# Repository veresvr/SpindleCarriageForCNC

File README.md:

# Spindle Carriage For CNC
:100: Project is done!

Milling carriage for my [laser CNC](https://github.com/veresvr/LaserCNCMachine)
All drawings available here [Drawings](https://github.com/veresvr/SpindleCarriageForCNC/tree/main/Drawings/AllDrawings.pdf)

##### Rendering
</img>
##### Assembly structure
 </img>

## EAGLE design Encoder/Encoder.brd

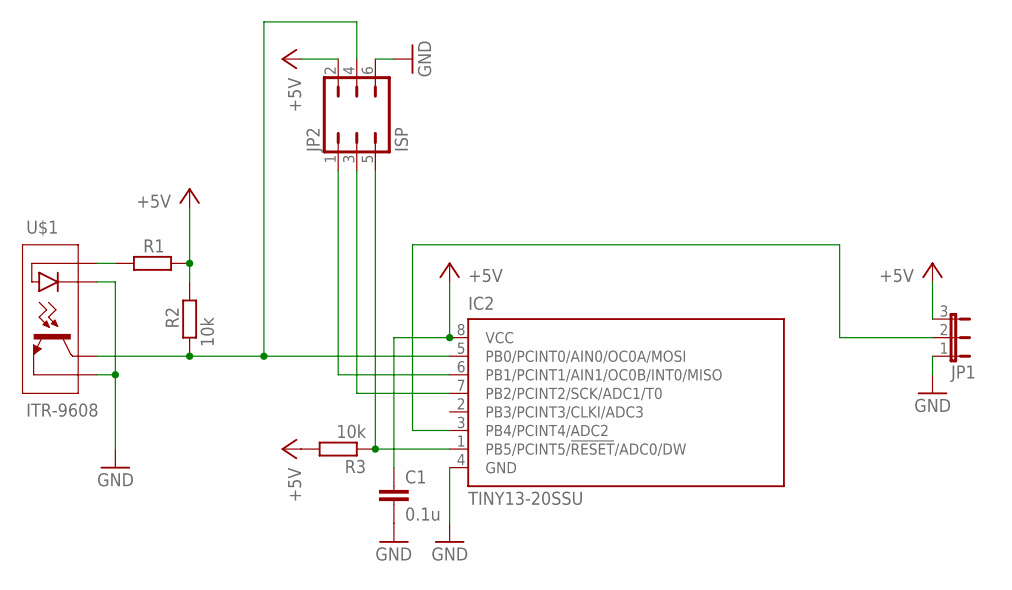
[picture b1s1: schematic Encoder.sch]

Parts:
C1: 0.1u; C0805
IC2: TINY13-20SSU; 8S1
JP1: JP2E; JP2
JP2: ISP; JP3Q
R1: R-EU_M0805; M0805
R2, R3: 10k; M0805
U$1: ITR-9608; ITR-9608-FOOTPRINT

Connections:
!RES: IC2.1 (PB5/PCINT5/!RESET!/ADC0/DW), JP2.5, R3.1
+5V: C1.1, IC2.8 (VCC), JP1.3, JP2.2, R1.2, R2.2, R3.2
DATA-IN: IC2.5 (PB0/PCINT0/AIN0/OC0A/MOSI), JP2.4, R2.1, U$1.C
DATA-OUT: IC2.3 (PB4/PCINT4/ADC2), JP1.2
GND: C1.2, IC2.4 (GND), JP1.1, JP2.6, U$1.E, U$1.K
unnamed: IC2.6 (PB1/PCINT1/AIN1/OC0B/INT0/MISO), JP2.1
unnamed: R1.1, U$1.A
unnamed: IC2.7 (PB2/PCINT2/SCK/ADC1/T0), JP2.3

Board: 2 copper layers, 8 parts (2 on the bottom side), 8 nets, no tracks yet.

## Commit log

2020-12-20 Some little bugs fixed
2021-01-02 Update files to SW2020. Some composition changes. Added more fasteners
2021-01-03 Some little composition changes.
2021-01-03 Simple motor encoder
2021-01-03 Change position of end sensors
2021-01-03 Decrease width of the CarriageBase
2021-01-03 Update CarriageBase
2021-01-05 Replace some screws
2021-01-05 Change geometry a little bit & add new screws
2021-01-07 Added ventilation holes to carriage. Updated encoder
2021-01-07 A little geometric changes
2021-01-08 Changed geometry for possibility using some drills.
2021-01-08 Hide threaded rod in carriage Z for decrease height
2021-01-10 Was decreased width in VerticalPlate
2021-01-10 A little changes in carriage cower
2021-01-16 Almost done the end sensors assembly
2021-01-17 End sensors assembly done. Added some little changes to VerticalPlate
2021-01-20 Changed lead screw length. Added some wires
2021-01-22 A little changes with cables and encoder
2021-01-30 Added mount to encoder
2021-01-31 Added motor & encoder wires
2021-02-10 Update motor mount
2021-02-22 Updated mates
2021-05-12 Updated the readme file
2021-05-21 Updated some parts. Added a drawing for sensor mount
2021-06-05 Updated parts
2021-06-09 Added drawings, updated material properties and tolerances in the parts. Added BOM
2021-06-12 Updated properties in the parts and the assemblies, updated the BOM. Added internet links to some positions in the BOM
2021-06-13 Added cable to the stepper, updated end sensor wire
2021-06-23 Added a scheme and a pcb for encoder
2021-06-27 Added a pcb for encoder: made scheme, library and prearranged components on the board
2021-06-27 Updated the assembly in case of encoder: added a pcb and updated the cover
2021-06-30 Added connector for programmer. Increased the place for the encoder.
2021-08-06 Added more powerful stepper motor
2021-08-07 Updated mount holes for the new stepper motor. Added cable for the stepper. Updated cable tie
2021-08-11 Tried making a new simplest tensioner
2021-08-20 Updated the tensioner and its mount.
2021-08-21 Updated the tensioner. Made TensionerBasePlate as a real part, updated properties, made drawing
2021-08-27 Updated the dimensions and tolerances in the tensioner plate. Updated some parameters in the parts.
2021-08-28 Updated properties for some parts. Updated tolerances. Added drawing numbers. Added some drawings
2021-08-29 Updated mount in motor holder
2021-09-13 Updated the drawing
2021-11-07 Added drawing for the tensioner and made it non virtual
2021-11-07 Added drawing for Carriage
2021-11-10 Updated the plastic mount brackets in the carriage
2021-11-11 Updated spacers and another part of the carriage
2021-11-20 Updated material in plastic parts.
2021-12-17 Packed all files into a single directory.
2021-12-18 Updated preview. Removed unnecessary stepper motor.
2022-01-02 Updated the main assembly structure. Updated drawings.
2022-01-02 Updated the main assembly structure. Moved some parts between subassemblies. Updated the main drawing.
2022-01-04 Replaced some screws, updated drawings.
2022-01-05 Changed exploded views, updated drawings.
2022-01-06 Saved some parts as non virtual, added drawings
2022-01-06 Added assembly structure
2022-02-03 Updated drawings
2022-02-05 Updated structure, parts and drawings.
2022-02-05 Updated the structure
2022-02-07 Updated dwg numbers
2022-02-10 Updated drawings and part properties.
2022-02-10 Updated the vertical plate
2022-02-11 Updated the vertical plate features and drawing
2022-02-13 Updated parameters in parts
2022-02-19 Updated BOMs
2022-02-26 Updated parts properties and drawings
2022-03-09 Added one more drawing
2022-03-15 Updated files location
2022-03-16 Added all drawings file and 3d pdf file
2022-06-25 added some chamfers, removed some geometry for best printing. updated parameter isFastener in parts
2022-08-14 some little changes. added drawings for polycarbonate production
2022-08-22 Updated some screws for unification
2022-08-24 updated motor cover
2022-08-26 updated belt and pulleys
2022-10-01 updated screws nut and motor cower. Updated the tensioner assembly.
2022-10-03 updated drawing
2022-10-07 added files for cnc
2022-10-15 updated some parts properties
2022-10-17 updated the motor holder
2022-10-29 added one drawing
2022-11-05 updated BOM
2022-11-05 updated main drawing
2022-11-12 added a clamp to the motor assembly
2022-11-12 updated drawings again
2022-11-18 Updated the drawings
2022-11-26 updated motor cowers and drawings
2022-11-27 updated file properties
2022-12-04 updated almost all drawings
2022-12-15 added 3d printed files
2022-12-17 Updated drawings, made the one with all
2022-12-18 removed temporary files
2022-12-18 renamed
2022-12-22 some little changes
2022-12-25 updated files
2023-01-01 fixed some bugs
2023-09-17 little updates & added igs
